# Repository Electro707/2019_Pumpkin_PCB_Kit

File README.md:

# 2019_Pumpkin_PCB_Kit
A soldering kit in the shape of a pumkpin. Designed for one of many UNH makerspace's soldering events

This repository is archived, as it's a one-time design.
Now files are hosted on Google Drive.

Link to website, in which the Google Drive link can be found:
[Link](https://electro707.com/documentation/PCB/2019_Pumpkin/index.php)

I may create a new general reposity for the kit that will be updated as time goes on 
(there also won't be any of the University of New Haven logos on that one).

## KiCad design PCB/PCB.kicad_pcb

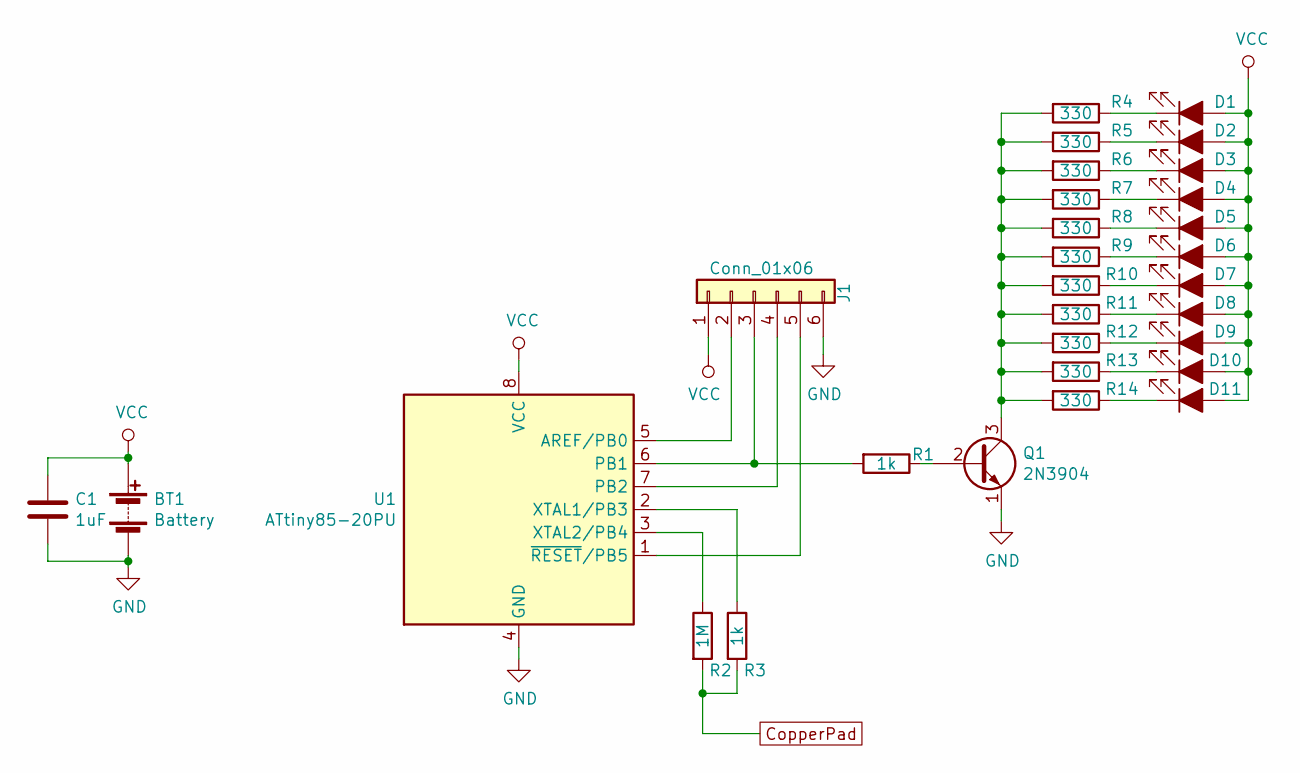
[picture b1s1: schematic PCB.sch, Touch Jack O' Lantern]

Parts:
BT1: Battery; BC2AAPC
C1: 1uF; C_1206_3216Metric_Pad1.42x1.75mm_HandSolder
D1, D2, D3, D4, D5, D6, D7, D8, D9, D10, D11: LED_ALT; LED_D5.0mm
J1: Conn_01x06; Tag-Connect_TC2030-IDC-NL_2x03_P1.27mm_Vertical
Q1: 2N3904; TO-92_Inline
R1, R3: 1k; R_1206_3216Metric_Pad1.42x1.75mm_HandSolder
R2: 1M; R_1206_3216Metric_Pad1.42x1.75mm_HandSolder
R4, R5, R6, R7, R8, R9, R10, R11, R12, R13, R14: 330; R_1206_3216Metric_Pad1.42x1.75mm_HandSolder
U1: ATtiny85-20PU; DIP-8_W7.62mm_Socket

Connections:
CopperPad: R2.2, R3.2
GND: BT1.2 (-), C1.2, J1.6, Q1.1 (E), U1.4 (GND)
unnamed: D1.1 (K), R4.1
unnamed: D2.1 (K), R5.1
unnamed: D3.1 (K), R6.1
unnamed: D4.1 (K), R7.1
unnamed: D5.1 (K), R8.1
unnamed: D6.1 (K), R9.1
unnamed: D7.1 (K), R10.1
unnamed: D8.1 (K), R11.1
unnamed: D9.1 (K), R12.1
unnamed: D10.1 (K), R13.1
unnamed: D11.1 (K), R14.1
unnamed: J1.2, U1.5 (AREF/PB0)
unnamed: J1.3, R1.2, U1.6 (PB1)
unnamed: J1.4, U1.7 (PB2)
unnamed: J1.5, U1.1 (~RESET~/PB5)
unnamed: Q1.2 (B), R1.1
unnamed: Q1.3 (C), R4.2, R5.2, R6.2, R7.2, R8.2, R9.2, R10.2, R11.2, R12.2, R13.2, R14.2
unnamed: R2.1, U1.3 (XTAL2/PB4)
unnamed: R3.1, U1.2 (XTAL1/PB3)
VCC: BT1.1 (+), C1.1, D1.2 (A), D2.2 (A), D3.2 (A), D4.2 (A), D5.2 (A), D6.2 (A), D7.2 (A), D8.2 (A), D9.2 (A), D10.2 (A), D11.2 (A), J1.1, U1.8 (VCC)

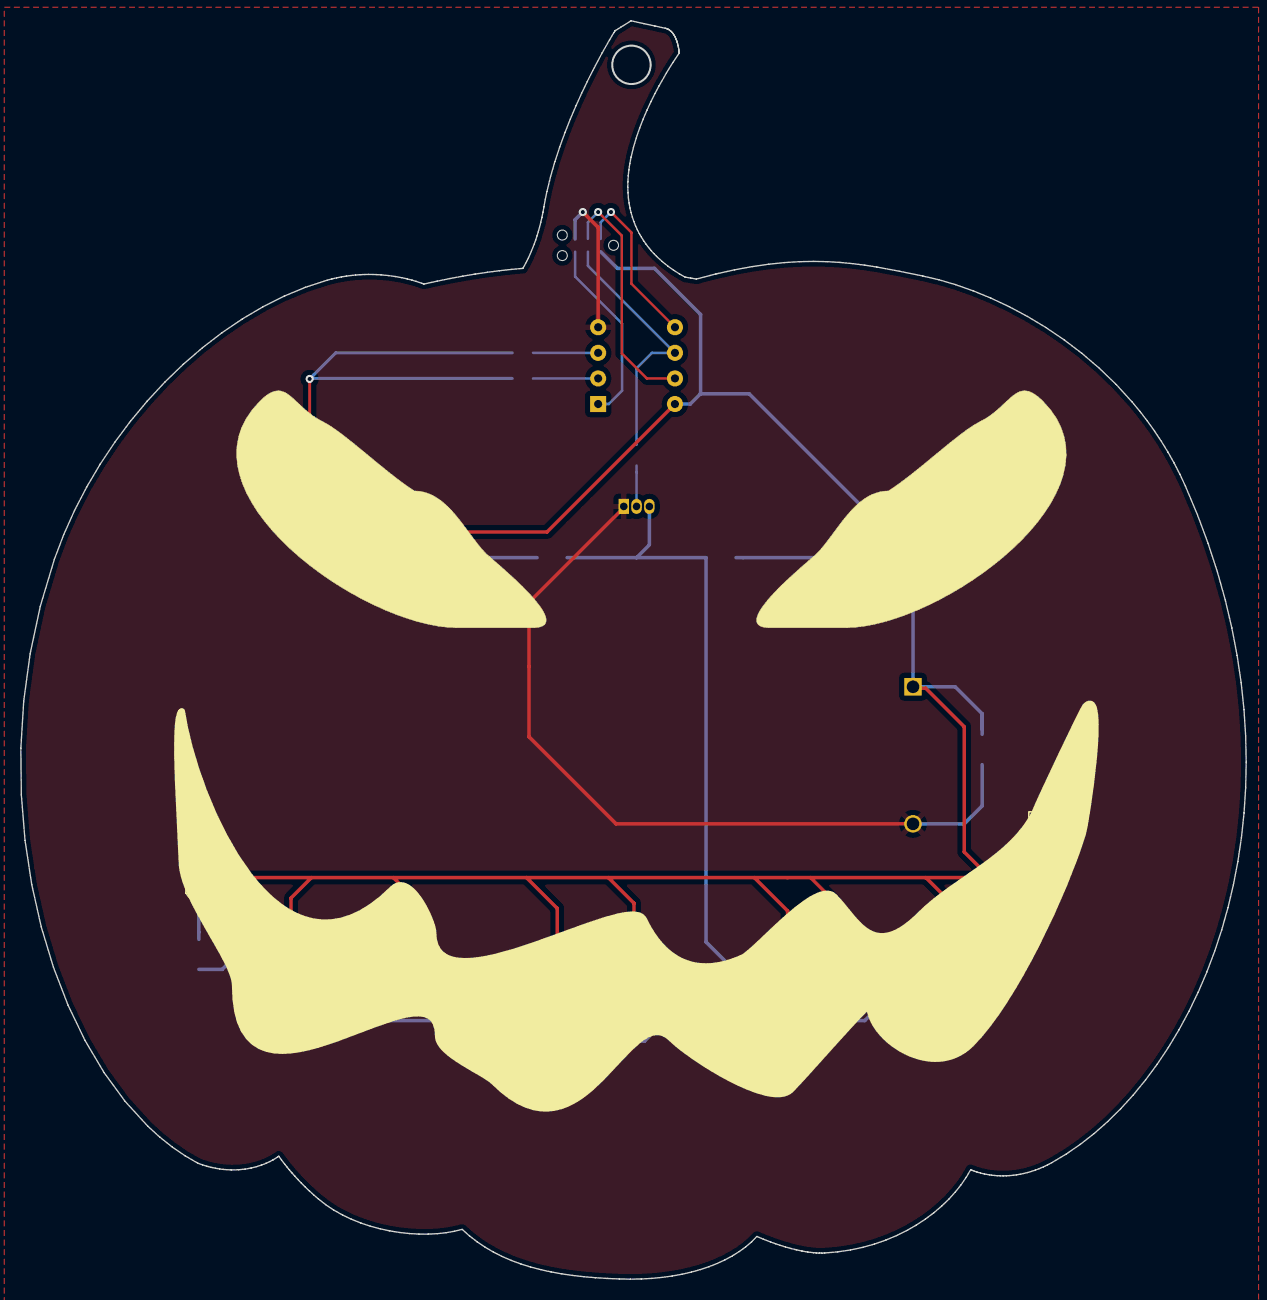
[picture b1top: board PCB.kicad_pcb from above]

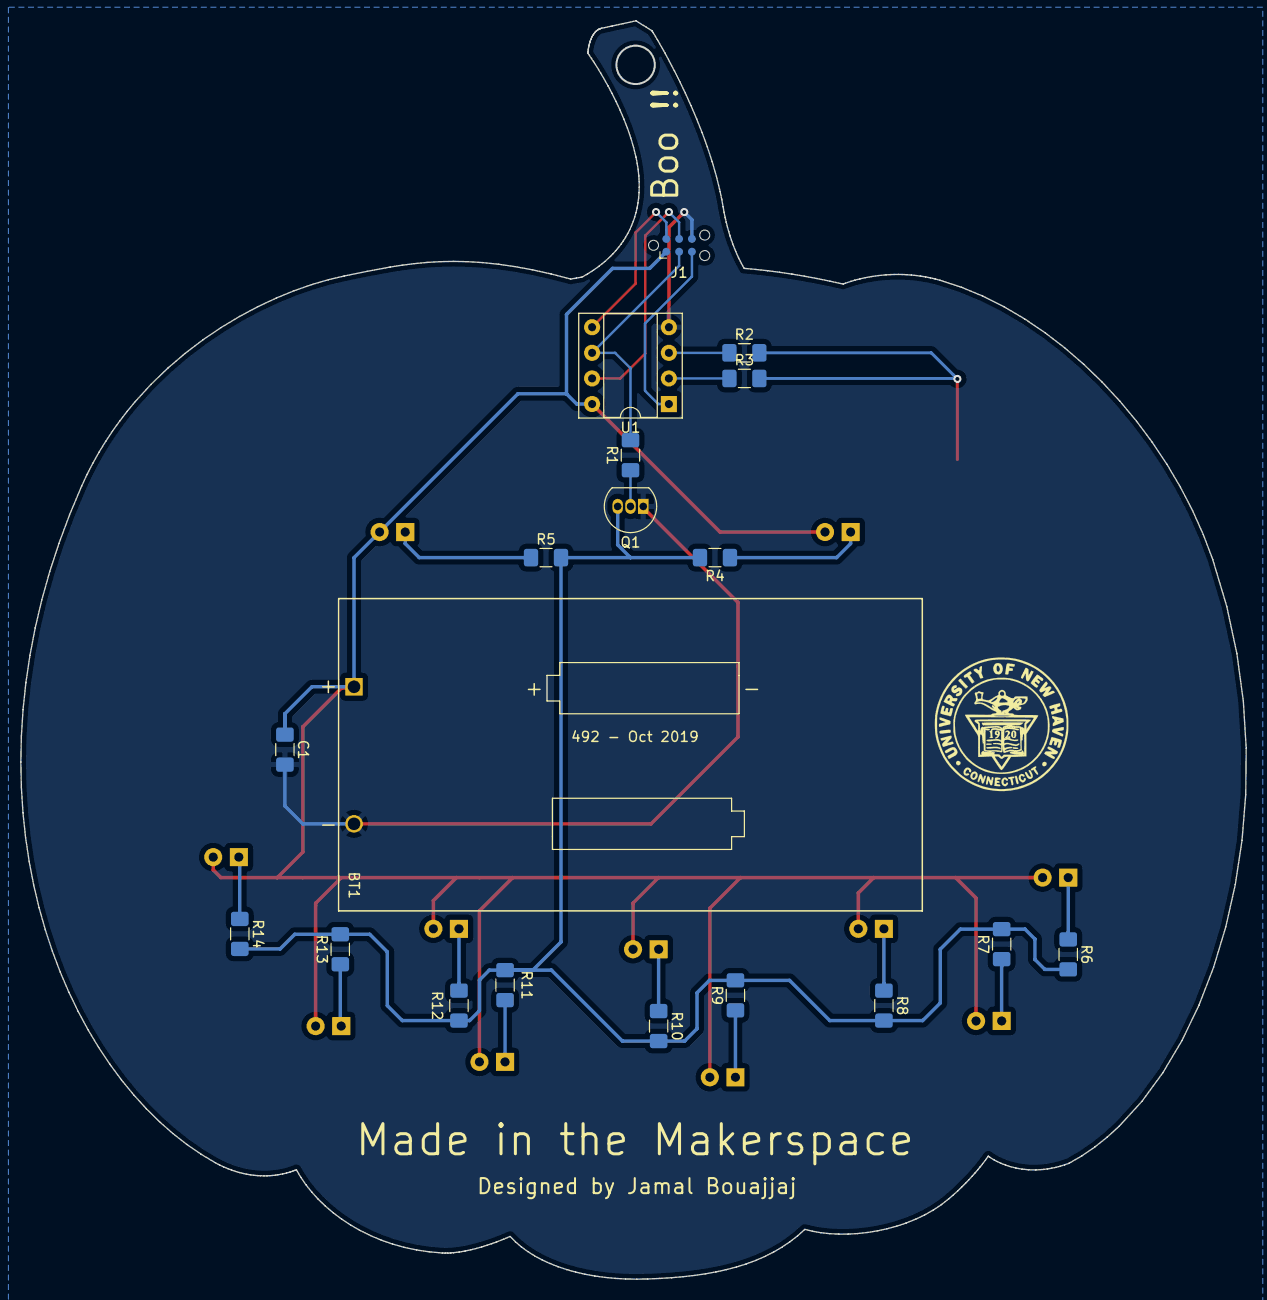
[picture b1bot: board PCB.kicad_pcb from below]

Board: 2 copper layers, 121.5 x 124.8 mm, 30 parts (19 on the bottom side), 22 nets.

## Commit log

2020-04-16 Pre-Archive Change
